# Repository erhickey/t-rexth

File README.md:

# Thyranathaurus Rexth

Several versions of a split keyboard I created using [Ergogen](https://github.com/ergogen/ergogen).

## [T-Rexth 36 Wired](./t-rexth-36-wired)

- 36 keys
- Split keyboard
- Ortholinear
- Wired
- MX switch compatible
- Hot swap sockets

## [T-Rexth 36](./t-rexth-36)

- 36 keys
- Split keyboard
- Ortholinear w/columnar stagger
- Wireless
- MX switch compatible
- Hot swap sockets
- Tenting puck compatible

## [T-Rexth 30](./t-rexth-30)

- 30 keys
- Split keyboard
- Ortholinear w/columnar stagger
- Wireless
- Choc switch compatible
- Minimal spacing
- Tenting puck compatible

# Credits/Thanks

- Created with [Ergogen](https://github.com/ergogen/ergogen) by [MrZealot](https://zealot.hu/)
- Motivated by [Ben Vallack's videos](https://www.youtube.com/channel/UC4NNPgQ9sOkBjw6GlkgCylg)
- [Guide](https://flatfootfox.com/ergogen-introduction/) by [FlatFootFox](https://flatfootfox.com/)
- Lots of help from members of [Ergogen Discord](https://discord.gg/nbKcAZB)
- Artwork by [Perce](https://madebyperce.com)
- Keycaps by [Pseudoku](https://github.com/pseudoku/PseudoMakeMeKeyCapProfiles)
- Tenting Puck by [lacohe](https://www.thingiverse.com/thing:5336898)

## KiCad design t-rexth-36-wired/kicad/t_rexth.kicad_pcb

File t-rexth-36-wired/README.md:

# Thyranathaurus Rexth

Under construction

## Firmware

[Example zmk configuration](https://github.com/erhickey/keyboards/tree/main/)

## Notes

Uses [infused-kim's](https://github.com/infused-kim) [reversible nice!nano footprint](https://github.com/infused-kim/kb_ergogen_fp/).

## Parts

In addition to the parts below a JST SH 4 pin cable and hotswap sockets are required.

| Type | Part | Details |
|------|-------------------------|----------------|
| Controller | [Adafruit KB2040 - RP2040 Kee Boar Driver](https://octopart.com/search?q=kb2040&currency=USD&specs=0) | [Adafruit](https://learn.adafruit.com/adafruit-kb2040) |
| Machine Pin Sockets | [Mill-Max 801 INTERCONNECT MACHINED PIN SOCKET](https://octopart.com/search?q=801-47-012-10-012000&currency=USD&specs=0) | [Mill-Max](https://www.mill-max.com/products/socket/801-xx-xxx-10-012000) |
| Socket Pins | [Mill-Max 3330 Straight Pin](https://octopart.com/search?q=3330-0-00-15-00-00-03-0&currency=USD&specs=0) | [Mill-Max](https://www.mill-max.com/products/pin/3330) |
| M2x8 Screws | [M2x8 Socket Hex Pan Head Screw](https://www.amazon.com/YXQ-Socket-Machine-Threaded-Knurled/dp/B01EZPNXZO?th=1) | Part Number: MT0502-004 - 3.8mm Head Diameter 2mm Head Height |
| M2 Threaded Insert | [M2 Female Thread Brass Threaded Insert](https://www.amazon.com/dp/B07LBQFNQD?th=1) | 3mm Length x 3.2mm OD |

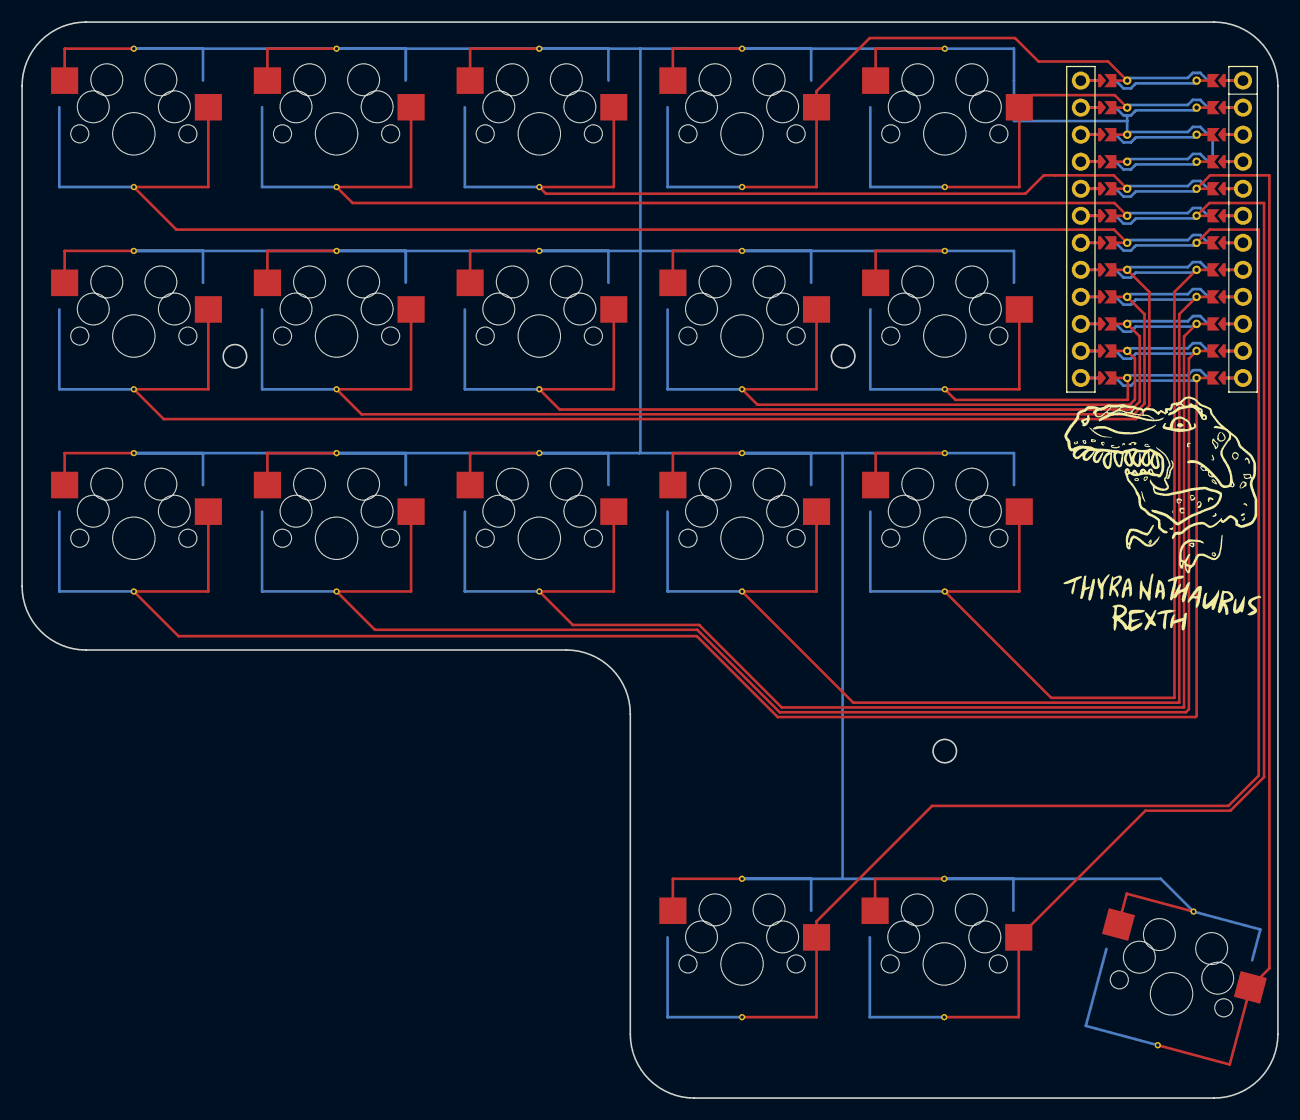
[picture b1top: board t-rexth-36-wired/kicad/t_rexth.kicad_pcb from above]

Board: 2 copper layers, 118.0 x 101.1 mm, 19 parts (0 on the bottom side), 19 nets.

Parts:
MCU1: nice_nano
S1, S2, S3, S4, S5, S6, S7, S8, S9, S10, S11, S12, S13, S14, S15, S16, S17, S18: MX_direct_reversible_hotswap

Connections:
GND: MCU1.2, MCU1.121, MCU1.122, S1.1, S1.2, S2.1, S2.2, S3.1, S3.2, S4.1, S4.2, S5.1, S5.2, S6.1, S6.2, S7.1, S7.2, S8.1, S8.2, S9.1, S9.2, S10.1, S10.2, S11.1, S11.2, S12.1, S12.2, S13.1, S13.2, S14.1, S14.2, S15.1, S15.2, S16.1, S16.2, S17.1, S17.2, S18.1, S18.2
P0: MCU1.123, S15.1
P1: MCU1.124, S12.1
P2: MCU1.120, S9.1
P3: MCU1.119, S6.1
P4: MCU1.118, S3.1
P5: MCU1.117, S2.1
P6: MCU1.116, S5.1
P7: MCU1.115, S8.1
P8: MCU1.114, S11.1
P9: MCU1.113, S14.1
P10: MCU1.12, S1.1
P14: MCU1.10, S7.1
P15: MCU1.9, S10.1
P16: MCU1.11, S4.1
P18: MCU1.8, S13.1
P19: MCU1.7, S16.1
P20: MCU1.6, S17.1
P21: MCU1.5, S18.1

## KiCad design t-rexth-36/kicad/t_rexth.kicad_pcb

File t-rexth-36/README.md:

# Thyranathaurus Rexth 36

## Notes

PCB track width and spacing is 0.15mm. Make sure your manufacturer is capable of printing boards with those specs. I used [JLCPCB](https://jlcpcb.com/capabilities/pcb-capabilities).

## Parts

| Type | Part | Manufacturer |
|------|-------------------------|----------------|
| Tactile Button | [C&K PTS636 SP43 LFS](https://www.mouser.com/ProductDetail/CK/PTS636-SP43-LFS?qs=vLWxofP3U2wWkB4yXWLrEg%3D%3D&utm_source=eciaauthorized&utm_medium=aggregator&utm_campaign=PTS636-SP43-LFS&utm_term=PTS636-SP43-LFS&utm_content=CK-Switches) | [C&K Switches](https://www.ckswitches.com/media/2779/pts636.pdf) |
| Slide Switch | [EAO 09.10290.01](https://www.mouser.com/ProductDetail/EAO/091029001?qs=2pKMaj72wiH1g4B38TGGGA%3D%3D&utm_source=eciaauthorized&utm_medium=aggregator&utm_campaign=091029001&utm_term=091029001&utm_content=EAO) | [EAO](https://eao.com) |
| Machine Pin Sockets | [Mill-Max 801 INTERCONNECT MACHINED PIN SOCKET](https://www.mouser.com/ProductDetail/Mill-Max/801-47-012-10-012000?qs=5aG0NVq1C4x40xNvDlnKzg%3D%3D) | [Mill-Max](https://www.mill-max.com/products/socket/801-xx-xxx-10-012000) |
| Socket Pins | [Mill-Max 3330 Straight Pin](https://www.mouser.com/ProductDetail/Mill-Max/3330-0-00-15-00-00-03-0?qs=s8Nb1z4Wn%2FSwJBcI97lmUw%3D%3D) | [Mill-Max](https://www.mill-max.com/products/pin/3330) |
| JST PH 2.0 Connector | [TE 1775469-2](https://www.mouser.com/ProductDetail/TE-Connectivity/1775469-2?qs=fvVej%2FMj3jdYOde%252BssG5lg%3D%3D) | [TE Connectivity](https://www.te.com/usa-en/product-1775469-2.html) |

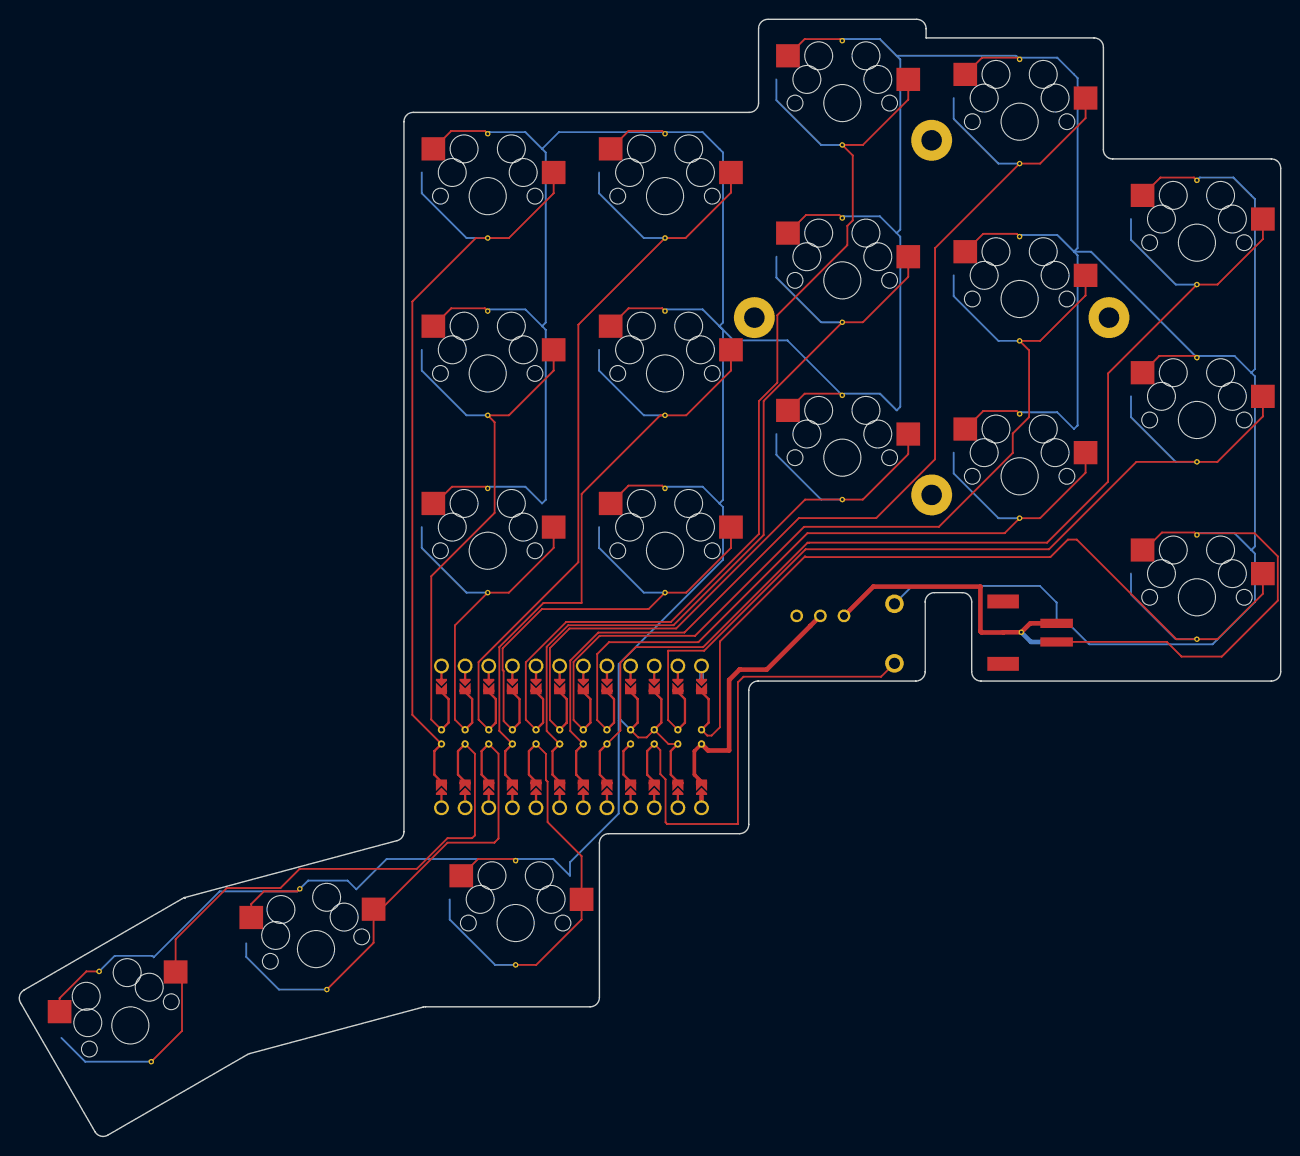
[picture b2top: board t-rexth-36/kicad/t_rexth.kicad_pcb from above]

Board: 2 copper layers, 135.5 x 120.0 mm, 23 parts (0 on the bottom side), 22 nets.

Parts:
B1: RST; PTS636
JST_PH_SMD1: 17754692
MCU1: ProMicro
S1, S2, S3, S4, S5, S6, S7, S8, S9, S10, S11, S12, S13, S14, S15, S16, S17, S18: MX
T1: SWITCH_09-10290_EOZ
_2: Tenting Puck

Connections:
BATT: JST_PH_SMD1.1, JST_PH_SMD1.2, T1.2
GND: B1.1, JST_PH_SMD1.1, JST_PH_SMD1.2, MCU1.2, MCU1.21, MCU1.22, S1.1, S1.2, S2.1, S2.2, S3.1, S3.2, S4.1, S4.2, S5.1, S5.2, S6.1, S6.2, S7.1, S7.2, S8.1, S8.2, S9.1, S9.2, S10.1, S10.2, S11.1, S11.2, S12.1, S12.2, S13.1, S13.2, S14.1, S14.2, S15.1, S15.2, S16.1, S16.2, S17.1, S17.2, S18.1, S18.2
P0: MCU1.23, S14.1
P1: MCU1.24, S13.1
P2: MCU1.20, S10.1
P3: MCU1.19, S11.1
P4: MCU1.18, S7.1
P5: MCU1.17, S9.1
P6: MCU1.16, S4.1
P7: MCU1.15, S6.1
P8: MCU1.14, S1.1
P9: MCU1.13, S2.1
P10: MCU1.12, S3.1
P14: MCU1.10, S17.1
P15: MCU1.9, S5.1
P16: MCU1.11, S18.1
P18: MCU1.8, S16.1
P19: MCU1.7, S8.1
P20: MCU1.6, S12.1
P21: MCU1.5, S15.1
RAW: MCU1.1, T1.1
RST: B1.2, MCU1.3

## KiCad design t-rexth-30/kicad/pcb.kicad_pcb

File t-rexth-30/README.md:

# Thyranathaurus Rexth 30

## Notes

This was my first attempt at building a custom keyboard, and has a couple issues:

- Attempting to solder battery wires onto the PCB without shorting your battery can be tricky.
- The spacing between the innermost columns is not wide enough, thus the philadelphia minimalist keycaps [do not fit both columns](./images/choc30_single.jpg).

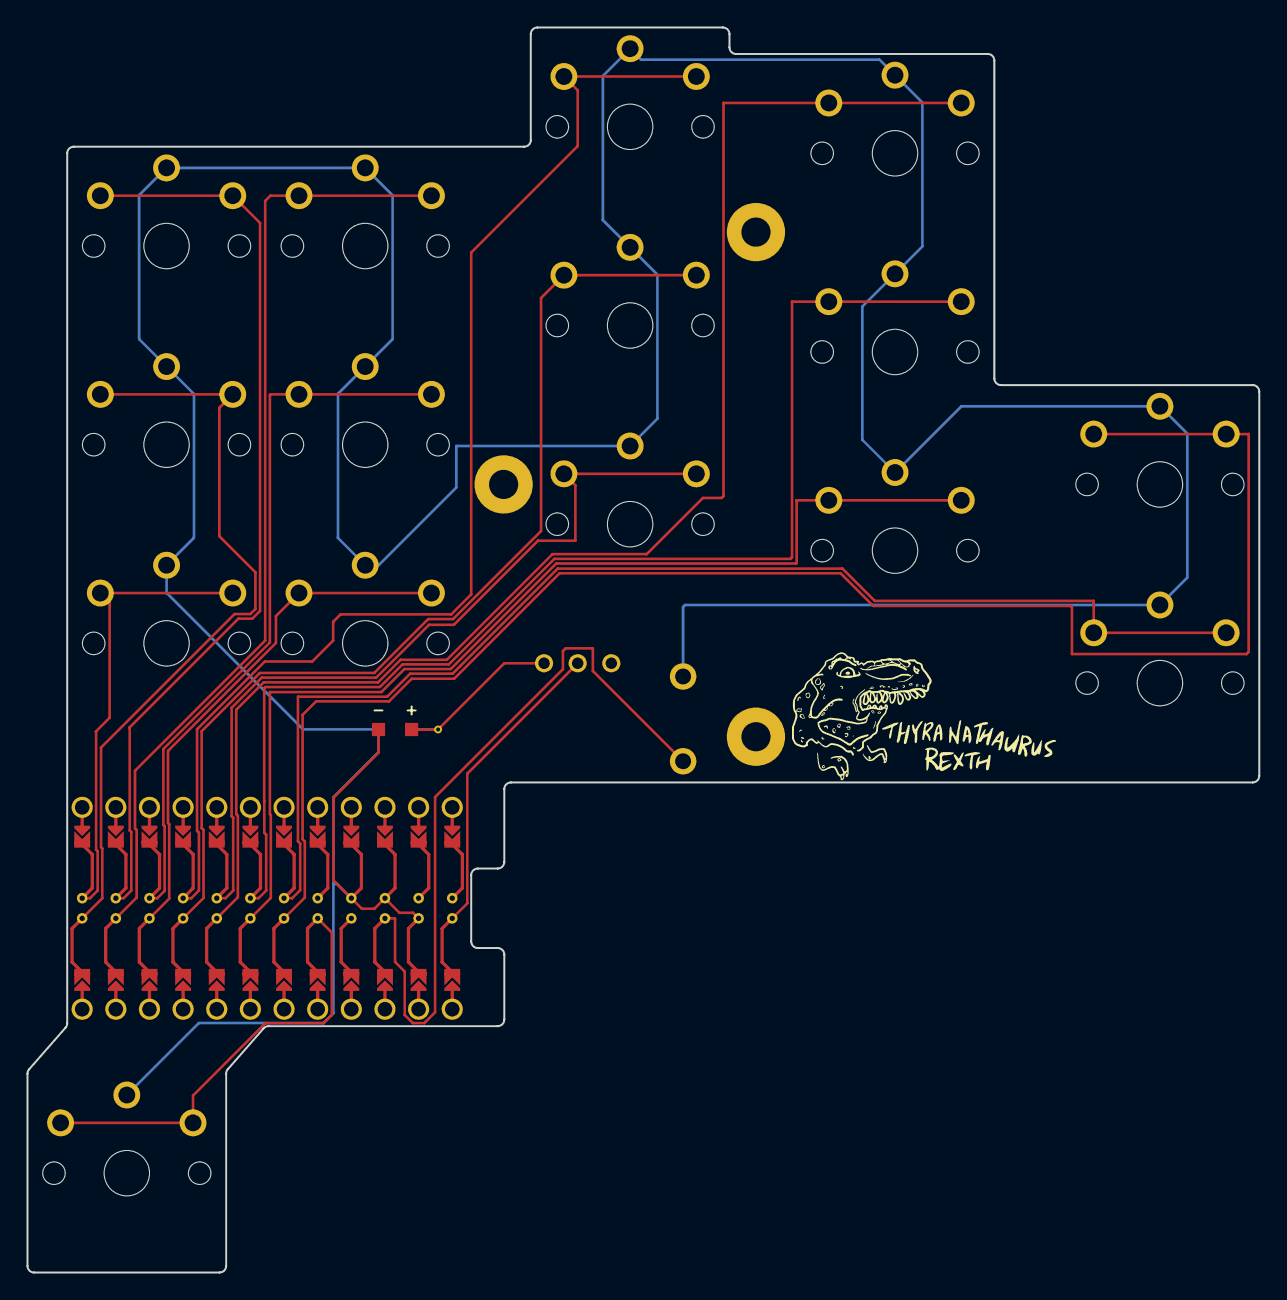
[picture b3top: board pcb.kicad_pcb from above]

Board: 2 copper layers, 93.0 x 94.0 mm, 21 parts (0 on the bottom side), 19 nets.

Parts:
B1: RST; PTS636
MCU1: ProMicro
PAD1, PAD2: SMDPad
S1, S2, S3, S4, S5, S6, S7, S8, S9, S10, S11, S12, S13, S14, S15: PG1350
T1: SWITCH_09-10290_EOZ
_2: Tenting Puck

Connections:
BATT: PAD1.1, T1.3
GND: B1.1, MCU1.2, MCU1.21, MCU1.22, PAD2.1, S1.2, S2.2, S3.2, S4.2, S5.2, S6.2, S7.2, S8.2, S9.2, S10.2, S11.2, S12.2, S13.2, S14.2, S15.2
P3: MCU1.19, S13.1
P4: MCU1.18, S11.1
P5: MCU1.17, S7.1
P6: MCU1.16, S9.1
P7: MCU1.15, S5.1
P8: MCU1.14, S3.1
P9: MCU1.13, S1.1
P10: MCU1.12, S2.1
P14: MCU1.10, S4.1
P15: MCU1.9, S8.1
P16: MCU1.11, S6.1
P18: MCU1.8, S12.1
P19: MCU1.7, S10.1
P20: MCU1.6, S14.1
P21: MCU1.5, S15.1
RAW: MCU1.1, T1.1
RST: B1.2, MCU1.3
